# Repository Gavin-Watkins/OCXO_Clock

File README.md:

# OCXO_Clock
Circuits, details and code for an Arduino based clock that uses a 10 MHz OCXO as a reference. 
# Introduction
This project describes a digital clock that uses a 10 MHz reference oscillator as its timing reference. This opens the possiblity of using a high stability OCXO reference to ensure high precision, beyond that of the convnetional clock. 
Precise time and frequency is an important requirement in many scientific applications. This used to be way beyond the scope of budget of many enthusiasts. There are those out there who go with the nickname Time Nut who scour online auctions for vintage atomic references like a Hewlett Packard 5061B Caesium clock so that they can poses a frequency reference with a stability accuracy of 2x10^-12. Recently these have come down in price to the point with Microchip offering a Rubidium Oscillator in a small compact package with an accuracy of <5x10^-11 for $2000. These may be beyond the scope of many, but temperature controlled crystal oscillators (TCXO) and oven controlled crystal oscillators (OCXO) with accuracies of 1x10^-6 and 5x10^-8 respectably. This is far better than the typical 20x10-6 of the 32.768 kHz crystals used in most digital clocks and the DS3231 which forms the basis of many digital clocks implemented on an Arduino or other micro-controller based platforms. Even worse is the 0.5% accuracy of the ceramic resonators used by the Arduino as a clock.
There are of course other options. Here in the UK the MSF transmissions at 60 kHz can be picked up by alarm clocks and watches to offer 2x10^-12 accuracy at home. Similar for the DCF77 in Germany at 77 kHz and WWV in the USA. GPS reception also offers an accuracy of 3x10^-8. All of this pushes the desire for a clock with an accuracy which is better than possible by the conventional 32.768 kHz crystal. This was the inception for this project, what accuracy is possible using modern crystal oscillators. 10 MHz has become the standard frequency for references, and so from hereon, it is assumed that this will be used. This project is highly flexible by its nature, so references with others frequencies could easily be used if desired.
# An OCXO Digital Clock
Previous work in this area had resulted in a divider chain to produce 32.768 kHz from 10 MHz. This was achieved by dividing 10 MHz by 1.25 x 2.5^6 using 74XX series discrete logic. The objective with this project was to build a clock from the ground up which could offer an accuracy far beyond anything which was consumer available. Although there is an appeal to building a clock completely in discrete logic, that limits the displays to generally seven segment LED types. For more complex displays, a micro-controller platform offers more options. The basic platform here is an Arduino Nano which offers far more processing power than is necessary for performing a simple hours-minutes-seconds type clock but is cheap and simple to use. There are many designs available online for such clocks, but they all inevitably rely on the DS3231 real-time clocks with its 2x10^-6 accuracy. One option could have been to drive the DS3231 with the divider chain mentioned above, but this was considered messy and would not really provide any great advantage.
The Arduino uses a 16 MHz ceramic resonator for its clock as mentioned above. It is not easy to change the frequency of this, to say 10 MHz without modify the firmware, and 16 MHz is used to derive the USB communications timing. Internet searches did not find any Arduino based clocks which used an external crystal reference surprisingly, so that was not an option. A physical switch to switch between 16 MHz and 10 MHz was an option, but not very practical. 
All microprocessors includes interrupts, which when triggered can pause the normal code running, move the registers to a memory location, carry out an interrupt service routine and then return to normal operation. These can generally be triggered by a clock driven timer or an external input on a dedicated pin. The Arduino includes three interrupt timers 
Timer0 and Timer1 can also be driven by an external clock source through the T0 and T1 pins. Timer0 is 8-bits where as Timer1 is 16 bit. The prescalars allows 2N division up to 1024, but are only accessible through the internal clock source. Setting CS10,CS11 and CS12 selects the external clock, but doing so bypasses the prescalar 
When used with an external clock on T0 or T1, the signal is sampled relative to the system clock. Using a maximum Nyquist sampling factor of 2.5, a realistic maximum external input frequency of 6.4 MHz results. Adding a 4 bit binary counter after the 10 MHz reference results in a 625 kHz, which when divided by 62500 (<216) results in 10 Hz. This triggers the interrupts and a chain of counters for  seconds, minutes and hours as shown in Figure 3.
Further dividers are implemented in software to generate 1 Hz, and then units and tens of the seconds, minutes and hours as separate LED displays are used for each. This will be explained in a further section which details the software and hardware implementation. 
# Components
An Arduino Nano is chosen for the platform, as it offers the same capabilities as the bigger platforms but is in a more compact form factor and is very cheap. Like most cheaper platforms it uses a ceramic resonator for timing, making it unsuitable for any critical applications. It does however include the usual SPI and I2C interfaces which make it easy to interface to modern displays with built in drivers. 
The OCXO (X1) chosen is a Raltron Electronics OX4120A-D3-5-10.000-3.3 available from Digikey. Any suitable OCXO could be used, even one with a difference frequency by changing the divider ratio. It also comes in a standard 14-pin dual-in-package (DIP) package. As the most expensive component, during most of the development a standard low cost 10 MHz oscillator was used. All of the components used in this project are either in DIP format or available in DIP modules for easy construction. The PCB is produced in KiCad and is made available both as KiCad files and gerbers through github for others to modify under the creative commons licence (File: OCXO_Clock_code_03_08_23). This allows components of different layouts to be used for example. Similarly, the 4-bit binary counter (U3) between OCXO and Arduino is a 74HC191. Any binary counter could be substituted for this provided it provides division. 
The OCXO is a 3.3V part, so a LD1117V33C linear low-drop-out (LDO) voltage regulator U2 derived this from the 5V system voltage. The 74HC191’s inputs are compatible with 3.3V logic levels so a translator is not necessary. The regulator is not critical, alternative LDO or switching types could be used. A second identical regulator U3 provides 3.3V to the displays. 
# Display
The display chosen are six Adafruit CharliePlex FeatherWing (A2-A7). These consist of 7x15 pixel array of LEDs which can be driven individually in a graphical mode or using fonts built into the Adafruit_IS31FL3731 library. They are communicated with by an I2C. The address of each can be set to one of two values: by default 0x74 but you can be changed to 0x77 by bridging a link. To drive multiple displays an I2C expander chip the TCA9548A (A8) is used. It has the address 0x77 (TCAADDR). 
The procedure for driving the TCA9548A is that first a command is sent to it to direct the input data to one of eight outputs. Then the command for the display digit is sent. The TCA9548A is only available in a surface mounted (SMT) package, but is available from Adafruit as the 2717 break out board in a DIP adapter board. This is available through Digikey and other online sellers. 
The CharliePlex displays in this project they are driven graphically with a separate look-up-table (LUT) for each character (0-9) and a whole byte for each pixel storing either a 0 or a 1. Although inefficient in the amount of memory space it takes up, this allows custom fonts to be easily programmed. A separate variable is used to set the brightness of the display. This could allow for dimming the brightness of the display at night if required. 
The seconds-minutes divider and minutes-hours divider are two separate LEDs. These are toggled on and off at a rate of 0.5 Hz by the one second divider chain. Their function or operation could be easily changed by modify the software.
# Input Interface
A single rotary encoder with a momentary press switch is used as the user interface. This gives the clock a modern minimalist feel. Separate press switches could of course be used with only minimum changes to the hardware and/or software. The rotary encoder software aims to mimic the operation of a monostable to reduce the impact of switch bounce. It was largely successful, although a few erroneous counts got through. Alternative rotary encoder software could easily be substituted into the clock. Although the prototype was built on one printed circuit board, it was designed so that it could easily be cut into two, so one mounted behind the other with header connectors for a more compact layout. This is reflected in the schematic with J1-4. 
# Software Details
The software is available here. Only two libraries, the aforementioned Adafruit_IS31FL3731 and the common Wire which enables serial communication including I2C and SPI. Next is the LUTs for the display. It is obvious by looking at them which digits are stored in which LUT.
The setup checks that each of the displays is functioning correctly and will send a command over the serial interface if not. Next Timer1 is setup for an external clock and to divide by 62499. This is 62499 and not 62500 as one instruction is needed to reset the counter.
The primary function of the main loop is to call the rotary encoder subroutine. The encoder subroutine aims to mimic a monostable to eliminate switch bounce. The code could easily be change here by a user. The displays are also driven here, but only when a toggle bit is enabled from the interrupt timer. Driving the displays in the graphical mode requires individually programming each of the 105 LEDs (15x7). There is also a brightness variable here which is user settable and the variable for increasing the brightness of a digit when it is being set. 
The Timer1 interrupt service routine is next which is called ten times a second. It consists of the divider chain. The LEDs between the seconds and minutes, and the minutes and hours are flashed here. Their function could be easily changed if desired. The final subroutine tcaselect deals with the TCA9548A I2C expander chip.
# PCB Layout
The schematic is exported to KiCad’s PCB layout. The final board is not complex and designed as a double sided board which is easy to solder. It is designed to be easily broken into two sections along the two cutouts either with a saw or scoring and snapping. Pads are fitted so that headers can be soldered in to plug the boards one behind the other making a more compact form suited to a desk clock. In this form, the “top” board holds the display and rotary encoder, with all else on the back board. The rotary encoder is fitting in the centre of the board, but this could course be moved to elsewhere and attached via flying leads. The prototype PCB was ordered through JCL in China, but any PCB fabrication house could be used for this or builders could do it themselves with a chemical process or routing machine. A photograph of the final board is shown in Figure 5, note there were some were some errors in the original layout which have been corrected in the final layout in Github.
The bottom portion of the board contains the Arduino, the I2C expander, the OCXO, divider chain and voltage regulators. The voltage regulators are mounted with the tabs facing outwards so heatsinks can be fitted if required. This wasn’t found necessary in the prototype, but if for example the displays are driven at a high current it maybe necessary. If the boards are mounted one behind the other, they are placed back to back, so all the components will be accessible from the back of the clock. This will make the design easier to hack if required. M3 holes are fitted in the board for easy mounting and these line up for the upper and lower parts of the board if they are mounted back to back with headers. Metal spacers can be fitted to provide the correct clearance and mechanical stability. 
Two mounting holes are also fitted above and below the OCXO. This is to provide mechanical stability. The OCXO is a relatively heavy component and held into the board simply by four bits in a DIP socket. This is also mounted vertically, so not particularly stable. A piece of wire can be threaded through the two holes with its ends twisted together to hold the OCXO is place. Cable ties could also be used, or a clamp if available. 
There are two sets of schematics, PCBs and gerbers files. This is because the TCA9548A modules comes in two flavours. The Adafruit one has a spacing of 0.6 inches between the rows (the "N" version) and the modules available on ebay have a 0.7 inch spacing. Double check which one you are using before fabricating the PCBs.
# Accuracy
The OX4120A-D3-5-10.000-3.3 is a fixed OCXO – it does not allow the ability to adjust the frequency. Alternative OCXOs do by applying a control voltage to one of the pins. This decision was made as its stability was believed to be high enough. However, the PCB could be easily modified to incorporate a trimmer resistor, or one fitted on flying leads so it is easily accessible. The problem then resides of how to check the accuracy of the clock and calibrate if needed. This requires a higher accuracy reference clock. The best the author had in his lab was a HP 53150A frequency counter with its own OCXO reference. It was last calibrated in 2013. When measuring the OCXO reference the frequency on the counter fluctuated between 10,000,000 and 9,999,999. This suggests an agreement and hence accuracy of better than <10-7. Being newer, it is likely that the OCXO in this clock is better than HP counter! 
# Construction
This project features several modules which are fitted with headers. These could be soldered directly to the PCB, but for convenience female sockets should be fitted as described in the BOM. This will allow parts to be changed in they become damaged or just for easy modification. Similarly, ICs sockets are fitted for U3 (74HC191) and X1 (OCXO).

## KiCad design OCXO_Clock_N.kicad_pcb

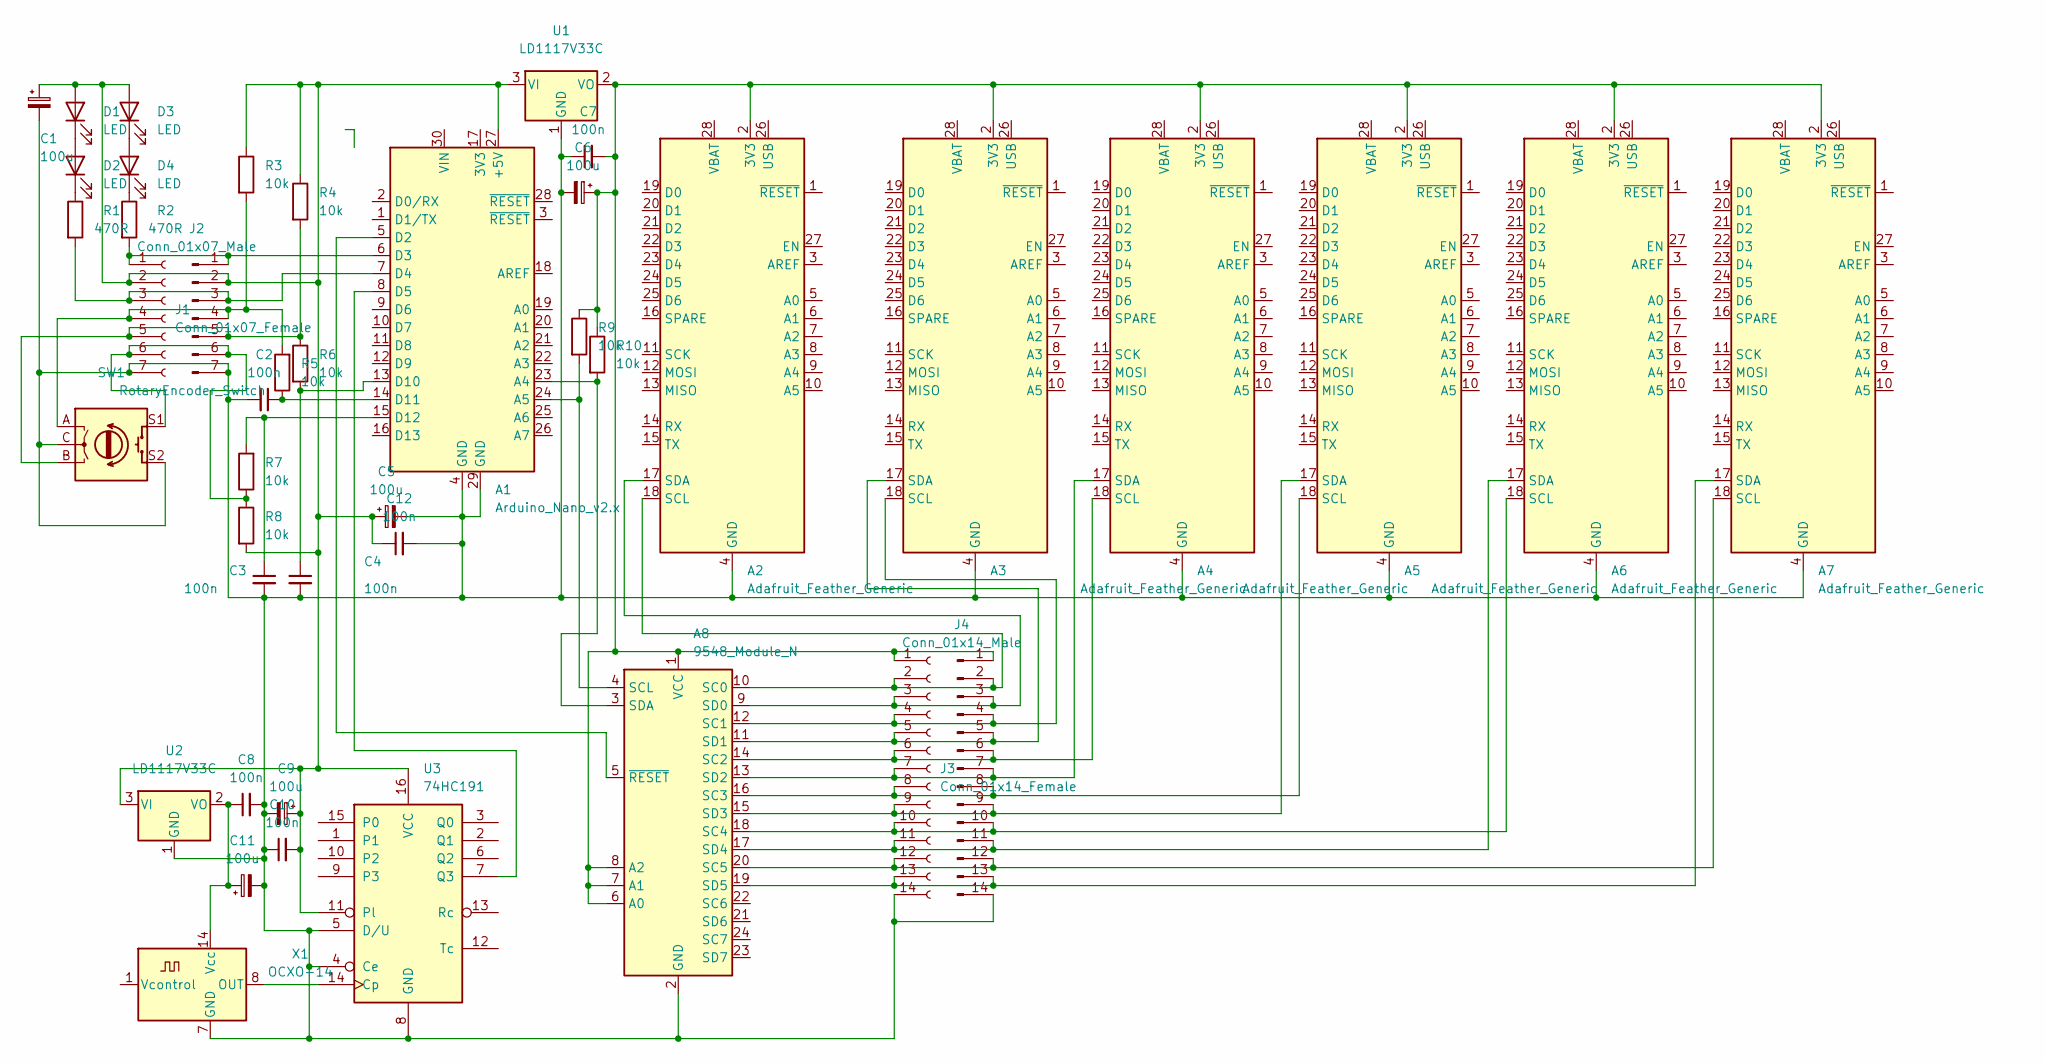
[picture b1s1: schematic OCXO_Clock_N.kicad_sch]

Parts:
A1: Arduino_Nano_v2.x; Arduino_Nano
A2, A3, A4, A5, A6, A7: Adafruit_Feather_Generic; Adafruit_Feather
A8: 9548_Module_N
C1, C5, C6, C9, C11: 100u; CP_Radial_D7.5mm_P2.50mm
C2, C3, C4, C7, C8, C10, C12: 100n; C_Rect_L7.0mm_W2.5mm_P5.00mm
D1, D2, D3, D4: LED; LED_D3.0mm
J1: Conn_01x07_Female; PinHeader_1x07_P2.54mm_Vertical
J2: Conn_01x07_Male; PinSocket_1x07_P2.54mm_Vertical
J3: Conn_01x14_Female; Molex_KK-254_AE-6410-14A_1x14_P2.54mm_Vertical
J4: Conn_01x14_Male; Molex_KK-254_AE-6410-14A_1x14_P2.54mm_Vertical
R1, R2: 470R; R_Axial_DIN0207_L6.3mm_D2.5mm_P10.16mm_Horizontal
R3, R4, R5, R6, R7, R8, R9, R10: 10k; R_Axial_DIN0207_L6.3mm_D2.5mm_P10.16mm_Horizontal
SW1: RotaryEncoder_Switch; RotaryEncoder_Bourns_Vertical_PEC12R-3xxxF-Sxxxx
U1, U2: LD1117V33C; TO-220-3_Vertical
U3: 74HC191; DIP-16_W7.62mm_LongPads
X1: OCXO-14; Oscillator_DIP-14

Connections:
unnamed: A1.5 (D2), A8.5 (~RESET)
unnamed: A1.6 (D3), J1.1, J2.1, R2.2
unnamed: A1.7 (D4), J1.3, J2.3, R1.2
unnamed: A1.8 (D5), U3.7 (Q3)
unnamed: A1.13 (D10), C4.1, R6.2
unnamed: A1.14 (D11), C2.1, R5.1
unnamed: A1.15 (D12), C3.1, R7.2
unnamed: A1.23 (A4), A8.3 (SDA), R10.2
unnamed: A1.24 (A5), A8.4 (SCL), R9.2
unnamed: A1.27 (+5V), C1.1, C5.1, C9.1, C10.2, C12.1, D1.2 (A), D3.2 (A), J1.2, J2.2, R3.1, R4.1, R8.2, U1.3 (VI), U2.3 (VI), U3.11 (Pl), U3.16 (VCC)
unnamed: A1.4 (GND), A1.29 (GND), A2.4 (GND), A3.4 (GND), A4.4 (GND), A5.4 (GND), A6.4 (GND), A7.4 (GND), A8.2 (GND), C1.2, C2.2, C3.2, C4.2, C5.2, C6.2, C7.1, C8.2, C9.2, C10.1, C11.2, C12.2, J1.7, J2.7, J3.14, J4.14, SW1.C, SW1.S2, U1.1 (GND), U2.1 (GND), U3.4 (Ce), U3.5 (D/U), U3.8 (GND), X1.7 (GND)
unnamed: A2.2 (3V3), A3.2 (3V3), A4.2 (3V3), A5.2 (3V3), A6.2 (3V3), A7.2 (3V3), A8.1 (VCC), A8.6 (A0), A8.7 (A1), A8.8 (A2), C6.1, C7.2, J3.1, J4.1, R9.1, R10.1, U1.2 (VO)
unnamed: A2.17 (SDA), A8.9 (SD0), J3.3, J4.3
unnamed: A2.18 (SCL), A8.10 (SC0), J3.2, J4.2
unnamed: A3.17 (SDA), A8.11 (SD1), J3.5, J4.5
unnamed: A3.18 (SCL), A8.12 (SC1), J3.4, J4.4
unnamed: A4.17 (SDA), A8.13 (SD2), J3.7, J4.7
unnamed: A4.18 (SCL), A8.14 (SC2), J3.6, J4.6
unnamed: A5.17 (SDA), A8.15 (SD3), J3.9, J4.9
unnamed: A5.18 (SCL), A8.16 (SC3), J3.8, J4.8
unnamed: A6.17 (SDA), A8.17 (SD4), J3.11, J4.11
unnamed: A6.18 (SCL), A8.18 (SC4), J3.10, J4.10
unnamed: A7.17 (SDA), A8.19 (SD5), J3.13, J4.13
unnamed: A7.18 (SCL), A8.20 (SC5), J3.12, J4.12
unnamed: C8.1, C11.1, U2.2 (VO), X1.14 (Vcc)
unnamed: D1.1 (K), D2.2 (A)
unnamed: D2.1 (K), R1.1
unnamed: D3.1 (K), D4.2 (A)
unnamed: D4.1 (K), R2.1
unnamed: J1.4, J2.4, R3.2, R5.2, SW1.A
unnamed: J1.5, J2.5, R4.2, R6.1, SW1.B
unnamed: J1.6, J2.6, R7.1, R8.1, SW1.S1
unnamed: U3.14 (Cp), X1.8 (OUT)

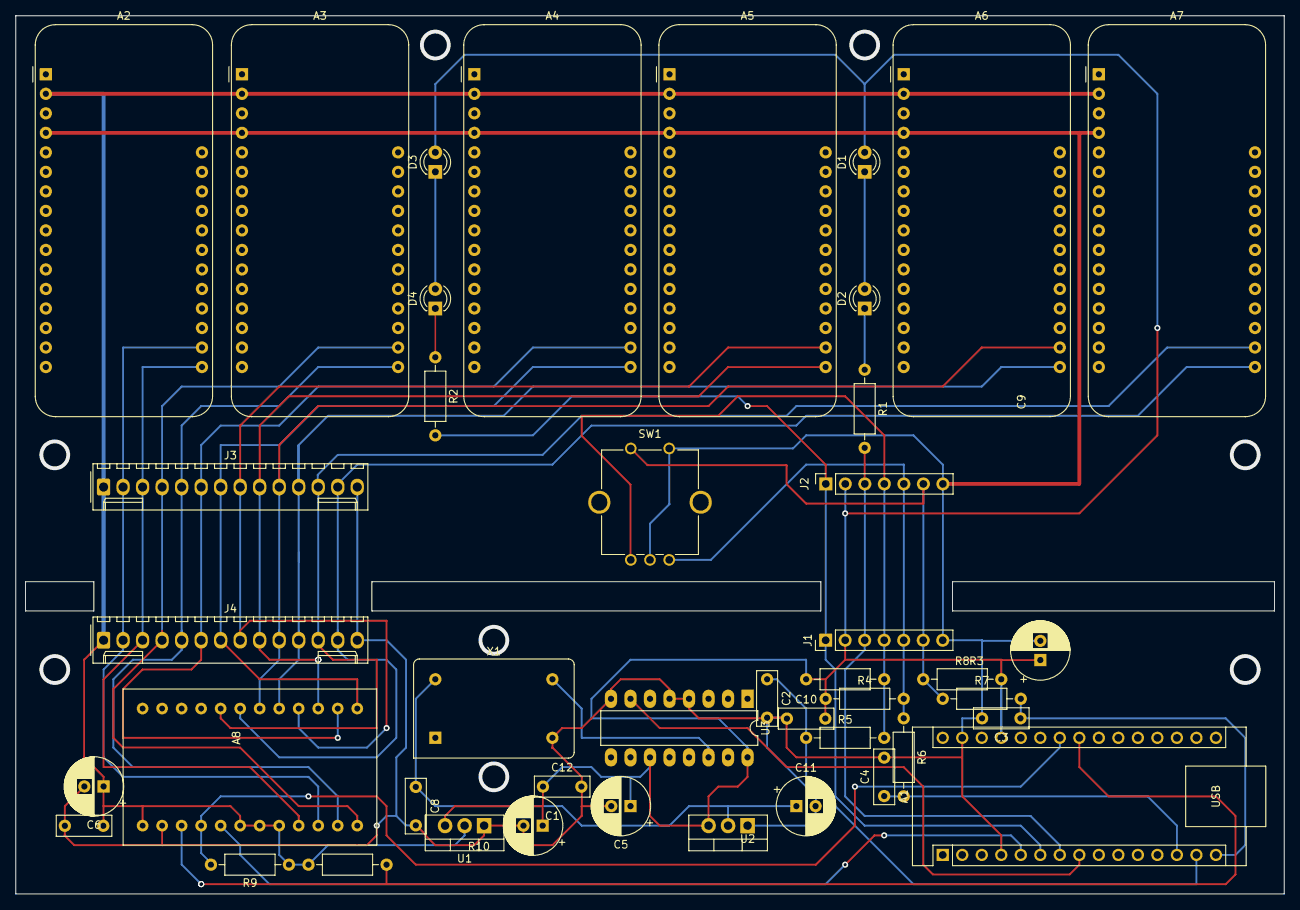
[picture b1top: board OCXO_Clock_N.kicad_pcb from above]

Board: 2 copper layers, 165.1 x 114.3 mm, 43 parts (0 on the bottom side), 33 nets.
